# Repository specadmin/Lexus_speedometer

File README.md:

# Модуль перевода показаний спидометра Lexus RX300 в километры в час #

Владельцы Lexus RX300 американского производства знают, что спидометр данного авто имеет две шкалы - крупную в милях в час и мелкую - в км/ч. В связи с этим считывание показаний спидометра в нужных нам единицах несколько затруднено. Предлагаемое устройство призвано решить эту проблему путем "переноса" действительных показаний спидометра в км/ч с мелкой шкалы на крупную.

Устройство подходит для приборных панелей Lexus RX300 1-го поколения (1998...2003).

Результат выглядит так:
<div align="center">  </div>

Элементы мелкой шкалы и MPH заклеиваются черной изолентой:
<div align="center">  </div>

Принципиальная схема устройства:
<div align="center">  </div>

Больше информации и инструкция по установке здесь: https://www.drive2.ru/l/583354966161298745/

## Готовый модуль ##

Для желающих получить результат быстрее в продаже есть готовые модули:
https://baza.drom.ru/krasnodar/sell_spare_parts/nabor-dlja-perevoda-pokazanij-spidometra-lexus-rx300-v-kilometry-v-chas-99117473.html

<div align="center">  </div>

## Готовая печатная плата ##

Также в продаже имеются печатные платы модуля: https://baza.drom.ru/krasnodar/sell_spare_parts/pechatnaja-plata-dlja-modulja-spidometra-lexus-rx300-99118293.html

<div align="center">  </div>

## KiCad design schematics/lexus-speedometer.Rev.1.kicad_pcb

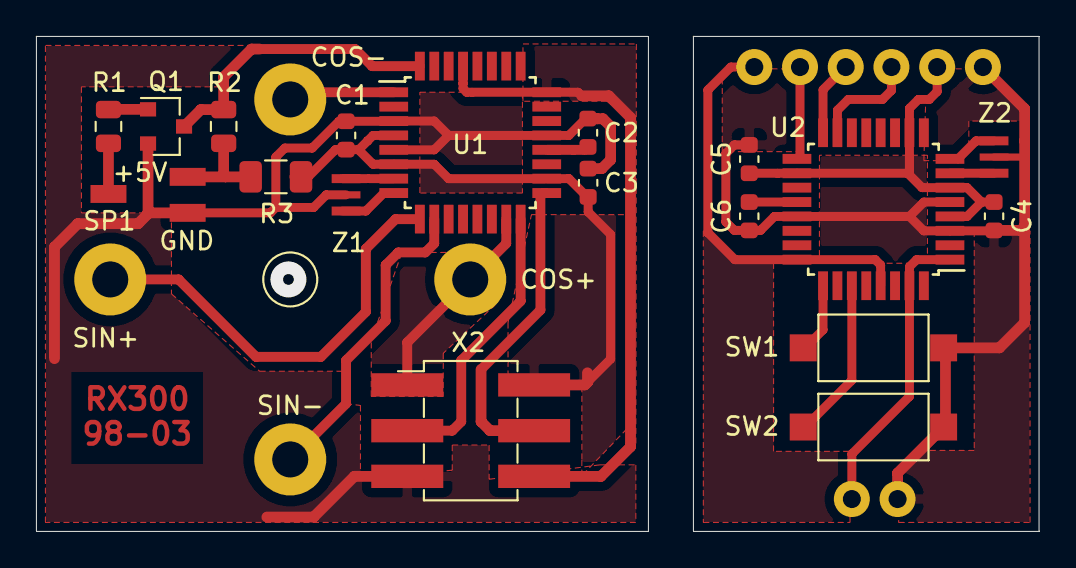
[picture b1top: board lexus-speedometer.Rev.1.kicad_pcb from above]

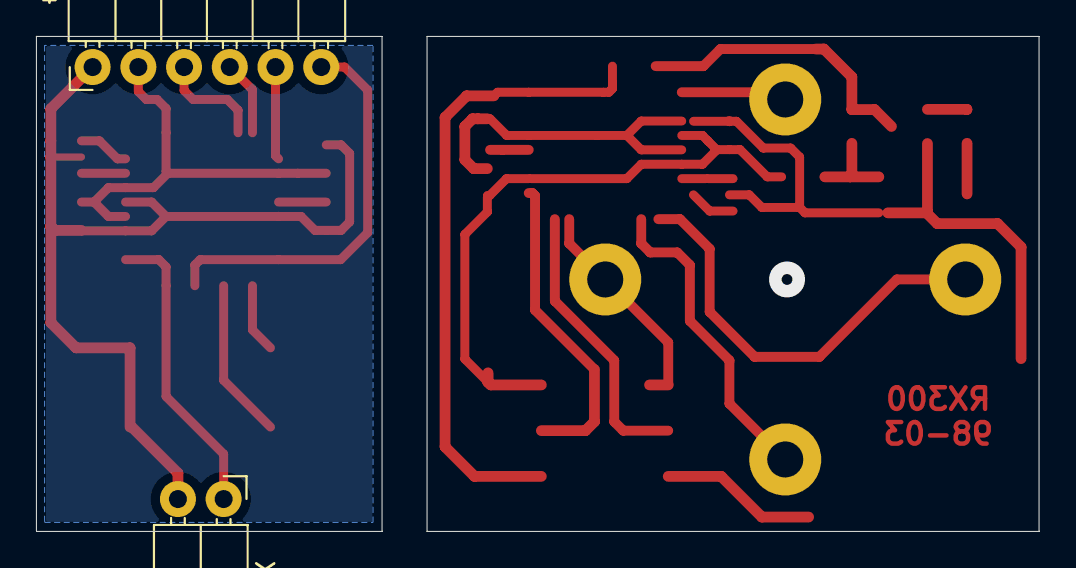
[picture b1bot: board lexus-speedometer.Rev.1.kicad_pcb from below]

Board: 2 copper layers, 55.7 x 27.5 mm, 23 parts (2 on the bottom side), 25 nets.

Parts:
+5V: Conn_01x01; Soldering_Pad_2.00mm_1.00mm
C1, C4: 10u; C_0603_1608Metric
C2, C3, C5, C6: 0.1; C_0603_1608Metric
GND: Conn_01x01; Soldering_Pad_2.00mm_1.00mm
Q1: 2SC2412; SOT-23
R1: 10k; R_0805_2012Metric
R2: 1k; R_0805_2012Metric
R3: 0; R_1206_3216Metric
SP1: Conn_01x01; Soldering_Pad_2.00mm_1.00mm
SW1: MORE; SW_SPST_CK_RS282G05A3
SW2: LESS; SW_SPST_CK_RS282G05A3
U1, U2: ATmega88; TQFP-32_7x7mm_P0.8mm
X1: SPEED; toyota_potentiometer
X2: SPI; PinHeader_2x03_P2.54mm_Vertical_SMD
X3: OUTPUT; PinHeader_1x02_P2.54mm_Horizontal
X4: SPI; PinHeader_1x06_P2.54mm_Horizontal
Z1, Z2: 16 MHz; Murata_CSTCExxxxV_3213_crystal

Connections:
+5V: C1.1, C3.1, C4.1, C5.1, R3.1, U1.4, U1.6, U1.18, U2.4, U2.6, U2.10, U2.18, X2.4, X4.2
/COS+: U1.15, X1.3, X2.1
/COS-: U1.1, X1.4
/SIN+: U1.9, X1.1
/SIN-: U1.10, X1.2
/VCC: +5V.1, R2.1, R3.2
GND: C1.2, C2.2, C3.2, C4.2, C5.2, C6.2, GND.1, Q1.2, SW1.1, SW2.1, U1.3, U1.5, U1.21, U2.3, U2.5, U2.21, X2.3, X3.2, X4.1, Z1.3, Z2.3
unnamed: C2.1, U1.20
unnamed: C6.1, U2.20
unnamed: Q1.1, R1.1
unnamed: Q1.3, R2.2, U1.32
unnamed: R1.2, SP1.1
unnamed: SW1.2, U2.25
unnamed: SW2.2, U2.27
unnamed: U1.7, Z1.1
unnamed: U1.8, Z1.2
unnamed: U1.16, X2.2
unnamed: U1.17, X2.5
unnamed: U2.1, U2.31, X3.1
unnamed: U2.7, Z2.1
unnamed: U2.8, Z2.2
unnamed: U2.15, X4.3
unnamed: U2.16, X4.4
unnamed: U2.17, X4.5
RST: U1.24, U1.29, U2.24, U2.29, X2.6, X4.6

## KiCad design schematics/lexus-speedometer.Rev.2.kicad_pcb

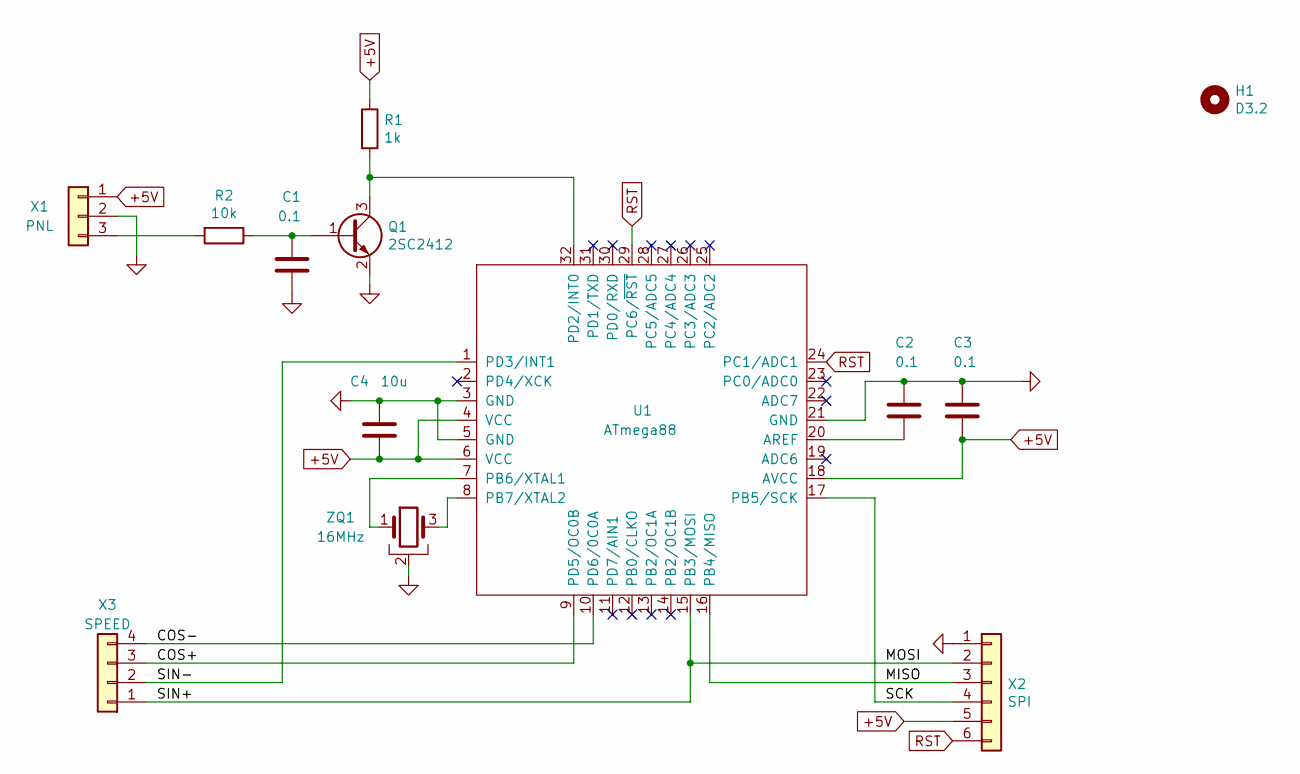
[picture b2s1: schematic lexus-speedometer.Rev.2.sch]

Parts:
C1, C2, C3: 0.1; C_0603_1608Metric
C4: 10u; C_0603_1608Metric
H1: D3.2; MountingHole_3.2mm_M3
Q1: 2SC2412; SOT-23
R1: 1k; R_0805_2012Metric
R2: 10k; R_0805_2012Metric
U1: ATmega88; TQFP-32_7x7mm_P0.8mm
X1: PNL; JST_PH_S3B-PH-SM4-TB_1x03-1MP_P2.00mm_Horizontal
X2: SPI; JST_PH_S6B-PH-SM4-TB_1x06-1MP_P2.00mm_Horizontal
X3: SPEED; toyota_potentiometer
ZQ1: 16MHz; Resonator_SMD_Murata_CSTxExxV-3Pin_3.2x1.3mm

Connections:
+5V: C3.1, C4.1, R1.1, U1.4 (VCC), U1.6 (VCC), U1.18 (AVCC), X1.1, X2.5
/COS+: U1.9 (PD5/OC0B), X3.3
/COS-: U1.10 (PD6/0C0A), X3.4
/MISO: U1.16 (PB4/MISO), X2.3
/MOSI: U1.15 (PB3/MOSI), X2.2, X3.1
/SCK: U1.17 (PB5/SCK), X2.4
/SIN-: U1.1 (PD3/INT1), X3.2
GND: C1.1, C2.2, C3.2, C4.2, Q1.2 (E), U1.3 (GND), U1.5 (GND), U1.21 (GND), X1.2, X1.MP, X2.1, X2.MP, ZQ1.2
unnamed: C1.2, Q1.1 (B), R2.1
unnamed: C2.1, U1.20 (AREF)
unnamed: Q1.3 (C), R1.2, U1.32 (PD2/INT0)
unnamed: R2.2, X1.3
unnamed: U1.7 (PB6/XTAL1), ZQ1.1
unnamed: U1.8 (PB7/XTAL2), ZQ1.3
RST: U1.24 (PC1/ADC1), U1.29 (PC6/~RST), X2.6

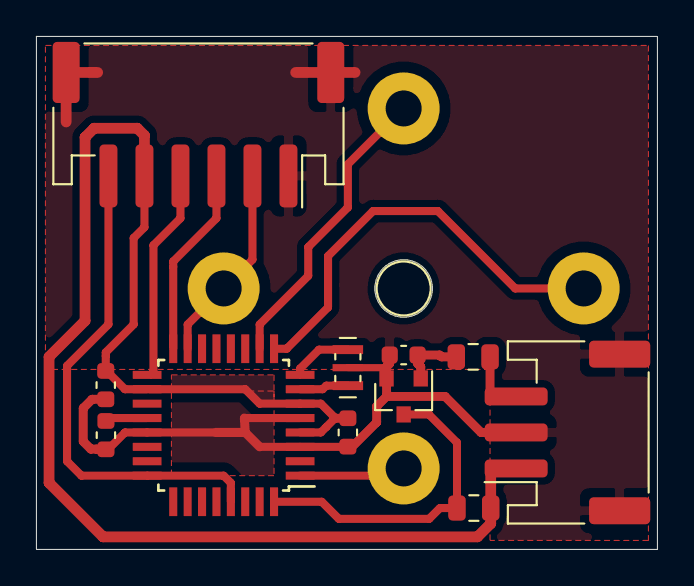
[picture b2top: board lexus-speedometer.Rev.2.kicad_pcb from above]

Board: 2 copper layers, 34.5 x 28.5 mm, 13 parts (0 on the bottom side), 15 nets.

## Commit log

2022-02-21 Description addedd
2022-02-21 Some pictures added
